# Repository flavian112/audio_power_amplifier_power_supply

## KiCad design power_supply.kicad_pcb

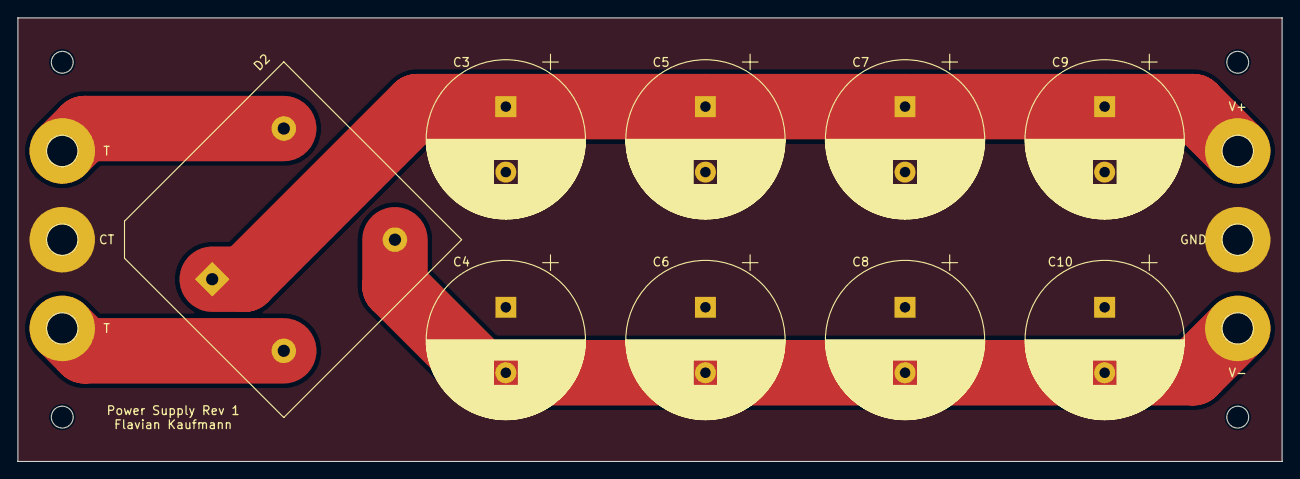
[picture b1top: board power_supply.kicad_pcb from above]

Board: 2 copper layers, 144.8 x 50.8 mm, 9 parts (0 on the bottom side), 3 nets.

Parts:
C3, C4, C5, C6, C7, C8, C9, C10: 2200u; CP_Radial_D18.0mm_P7.50mm
D2: D_Bridge_+A-A; Diode_Bridge_28.6x28.6x7.3mm_P18.0mm_P11.6mm

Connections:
+35: C3.1, C5.1, C7.1, C9.1, D2.1 (+)
-35: C4.2, C6.2, C8.2, C10.2, D2.3 (-)
GND: C3.2, C4.1, C5.2, C6.1, C7.2, C8.1, C9.2, C10.1

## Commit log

2024-02-04 cosmetics
